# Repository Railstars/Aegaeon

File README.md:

Aegaeon
=======

A feature-rich, NMRA standards compliant DCC decoder built around the Atmel ATtiny84A.

This project comprises hardware, firmware, and documentation for the Railstars Aegaeon series of [NMRA DCC decoders](http://en.wikipedia.org/wiki/Digital_Command_Control).

The Intent
----------

Let's be honest: Most decoders manufactured in North America kinda suck. We can do better. I want to harness the power of open source development to put together the finest range of decoders available, anywhere. This project has multiple goals:
* NMRA standard conformance
* Robustness: decoders should be fault-tolerant, and compatible with widest range of other DCC equipment
* Size: Modern technology permits really tiny decoders
* Features: There is no excuse not to have the best feature set possible

Hardware
--------

The hardware features an Atmel ATtiny84A microcontroller, a high-current H-Bridge with BEMF feedback, and two high-current open-collector outputs for lighting effects.

### Features

* Ultra-compact size (approx. 11mm x 6.7mm)
* 1A motor outputs
* Feedback motor control (aka BEMF)
* 16KHz or 32KHz motor operating modes
* Two high-current (300mA) function outputs
* Debugging header for use with DEBUGwire devices like Atmel JTAGICE mk2
* Trimming of internal RC oscillator is necessary for operation, requires Atmel AVRISP, a copy of stk500.exe, and MS DOS to calibrate. (Welcome to the 21st century!)

Firmware
--------

The firmware is written in pure C, and can be conditionally compiled for one of three possible configurations (motor only; motor + two functions; H-Bridge-driven function-only). Feature packed, and fully NMRA standards compliant, guaranteed by a stringent set of unit tests (in UnitTests folder, includes Xcode and NetBeans projects so you can run them straight on your Mac or PC).

### Features

* Momentum, 3-step and 28-step speed tables
* Button-controllable shunting mode
* Configurable function directionality, brightness, and Rule 17 dimming effects
* Configurable, button-controllable animations:
    * Strobe
    * Double strobe
    * Rotary beacon
    * Random flicker
    * Left/right ditch lights
    * Mars and Gyra lights
* Optional soft-start lighting effect
* Advanced consisting
* Supports Paged, Direct, Physical, and Operations mode programming
* Configurable DC operation, or stop-on-DC.

License
-------

The contents of the firmware folder is licensed under the GPLv3.
All other content is licensed under a Creative Commons Attribution-ShareAlike 3.0 Unported license

The Future
----------

There are a large number of features I would like to add to this product. I need your help!
- [ ] 2-layer PCB with easy-to-solder components for DIY
- [ ] ATmega328p/AT90CAN128 support for Arduino Uno/Railstars Io:duino
- [ ] Visual Studio project for unit tests
- [ ] Arduino project for easy integration into Arduino projects
- [ ] RailCom support (Railstars has a license to the necessary patents to implement RailCom, need to verify that implementing it as an open source project is kosher)
- [ ] On-the-tracks ops-mode bootloader. Ideally Arduino compatible but that might be a stretch. Would certainly require RailCom to work. But wouldn't that be awesome!?

Discussion
----------

You can get support for the Aegaeon software at the Railstars [Support Forum](http://support.railstars.com/index.php?p=/categories/aegaeon-firmware)

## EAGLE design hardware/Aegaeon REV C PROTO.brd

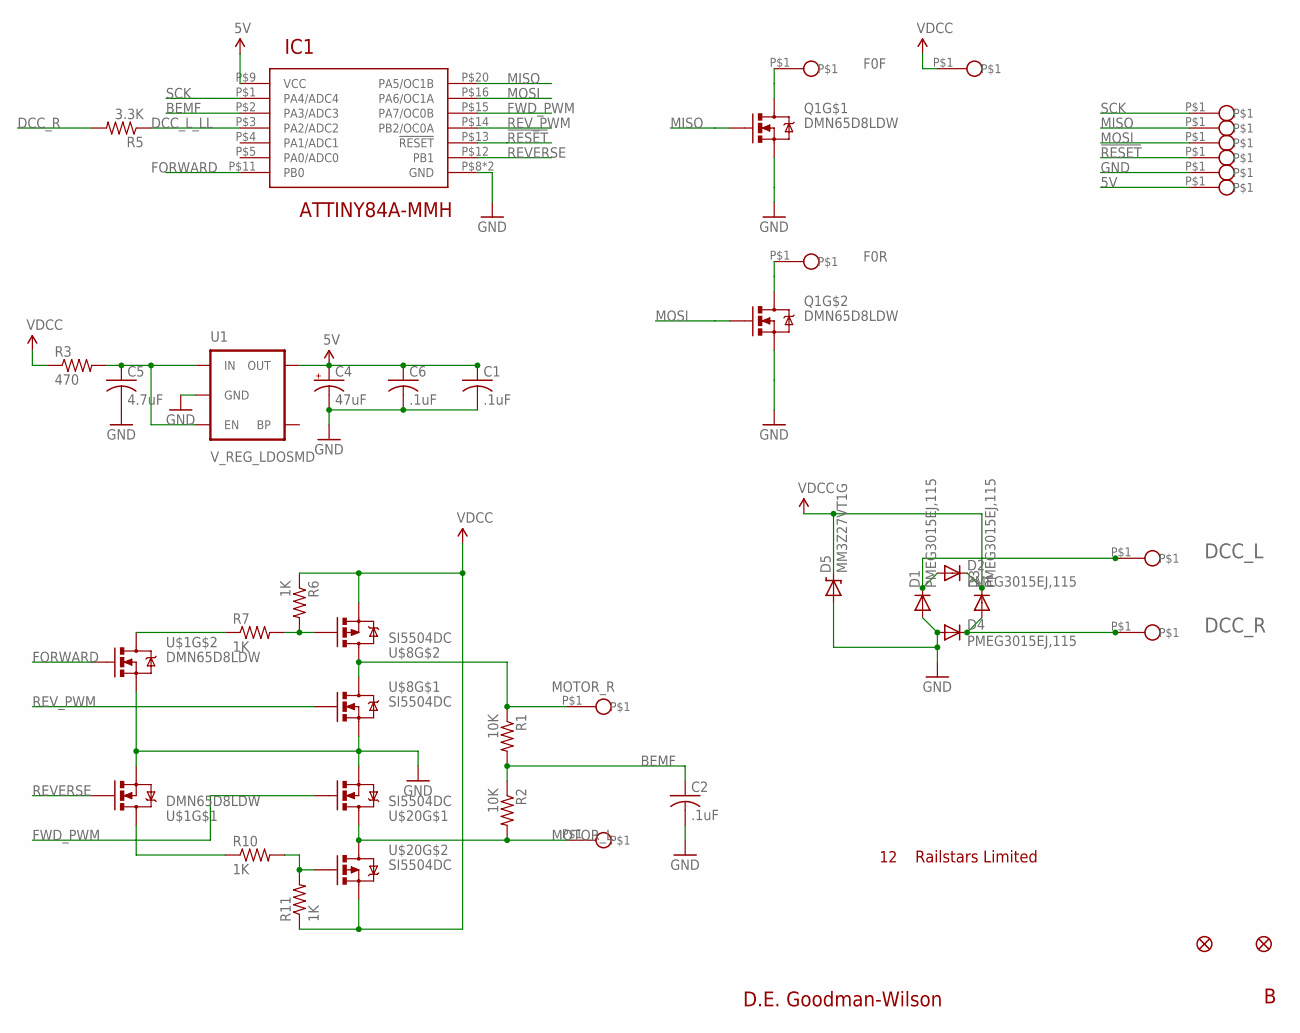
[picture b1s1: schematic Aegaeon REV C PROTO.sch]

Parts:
C1: .1uF; C0201
C2, C6: .1uF; C0402
C4: 47uF; CPOL0603
C5: 4.7uF; C0603
D1, D2, D3, D4: PMEG3015EJ,115; SOD-323
D5: MM3Z27VT1G; SOD-323
DCC_L: PAD1MM; LED_SOLDER_PAD
DCC_R: PAD1MM; LED_SOLDER_PAD
IC1: ATTINY84A-MMH; VQFN-20
JP2, JP4: FIDUCIALUFIDUCIAL; MICRO-FIDUCIAL
Q1: DMN65D8LDW; SOT363
R1, R2: 10K; R0201
R3: 470; R0201
R5: 3.3K; R0201
R6, R7, R10, R11: 1K; R0201
U1: V_REG_LDOSMD; SOT23-5
U$1: DMN65D8LDW; SOT363
U$2, U$3, U$5, U$10, U$11: PAD1MM; LED_SOLDER_PAD
U$8, U$20: SI5504DC; 1206-8
U$14, U$15, U$16, U$17, U$18, U$19: PAD.75MM; POGO_PAD

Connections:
5V: C1.1, C4.1 (+), C6.1, IC1.P$9 (VCC), U1.5 (OUT), U$19.P$1
!RESET: IC1.P$13 (!RESET), U$17.P$1
BEMF: C2.1, IC1.P$2 (PA3/ADC3), R1.2, R2.1
DCC_L: D1.1 (C), D2.2 (A), DCC_L.P$1
DCC_L_LL: IC1.P$3 (PA2/ADC2), R5.1
DCC_R: D3.2 (A), D4.1 (C), DCC_R.P$1, R5.2
F0F: Q1.P$4 (D), U$10.P$1
F0R: Q1.P$1 (D), U$5.P$1
FORWARD: IC1.P$11 (PB0), U$1.P$5 (G)
FWD_PWM: IC1.P$15 (PA7/OC0B), U$20.P$2 (G)
GND: C1.2, C2.2, C4.2 (-), C5.2, C6.2, D1.2 (A), D4.2 (A), D5.2 (A), IC1.P$8 (GND), IC1.P$21 (GND), Q1.P$3 (S), Q1.P$6 (S), U1.2 (GND), U$1.P$3 (S), U$1.P$6 (S), U$8.P$1 (S), U$18.P$1, U$20.P$1 (S)
MISO: IC1.P$20 (PA5/OC1B), Q1.P$2 (G), U$15.P$1
MOSI: IC1.P$16 (PA6/OC1A), Q1.P$5 (G), U$16.P$1
MOTOR_L: R2.2, U$3.P$1, U$20.P$5 (D), U$20.P$6 (D), U$20.P$7 (D), U$20.P$8 (D)
MOTOR_R: R1.1, U$2.P$1, U$8.P$5 (D), U$8.P$6 (D), U$8.P$7 (D), U$8.P$8 (D)
unnamed: R6.2, R7.2, U$8.P$4 (G)
unnamed: C5.1, R3.2, U1.1 (IN), U1.3 (EN)
unnamed: R10.2, R11.2, U$20.P$4 (G)
unnamed: R10.1, U$1.P$4 (D)
unnamed: R7.1, U$1.P$1 (D)
REVERSE: IC1.P$12 (PB1), U$1.P$2 (G)
REV_PWM: IC1.P$14 (PB2/OC0A), U$8.P$2 (G)
SCK: IC1.P$1 (PA4/ADC4), U$14.P$1
VDCC: D2.1 (C), D3.1 (C), D5.1 (C), R3.1, R6.1, R11.1, U$8.P$3 (S), U$11.P$1, U$20.P$3 (S)

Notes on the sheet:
Railstars Limited
D.E. Goodman-Wilson

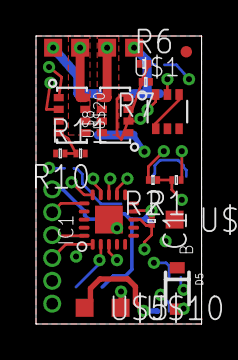
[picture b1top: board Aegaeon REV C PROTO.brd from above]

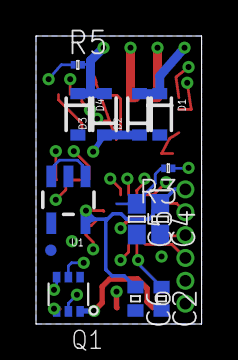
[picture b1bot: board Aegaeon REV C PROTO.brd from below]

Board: 4 copper layers, 9.2 x 16.0 mm, 39 parts (13 on the bottom side), 24 nets.

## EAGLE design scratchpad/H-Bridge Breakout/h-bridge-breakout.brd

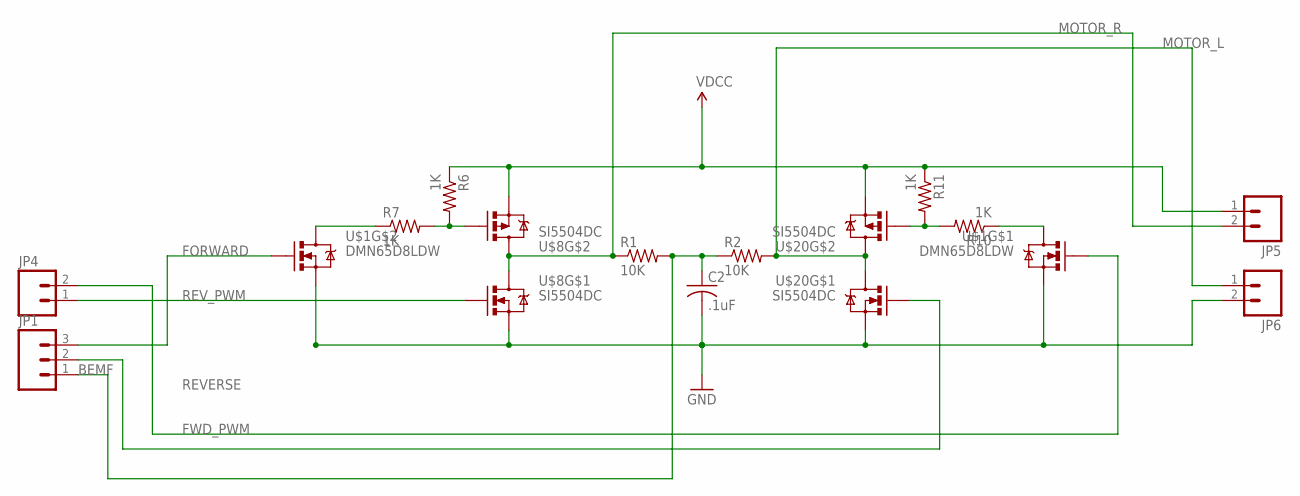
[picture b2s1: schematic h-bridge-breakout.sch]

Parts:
C2: .1uF; C0402
JP1: M03SCREW; SCREWTERMINAL-3.5MM-3
JP4, JP5, JP6: M023.5MM; SCREWTERMINAL-3.5MM-2
R1, R2: 10K; R0603
R6, R7, R10, R11: 1K; R0603
U$1: DMN65D8LDW; SOT363
U$8, U$20: SI5504DC; 1206-8

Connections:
BEMF: C2.1, JP1.1, R1.2, R2.1
FORWARD: JP1.3, U$1.P$5 (G)
FWD_PWM: JP1.2, U$20.P$2 (G)
GND: C2.2, JP6.2, U$1.P$3 (S), U$1.P$6 (S), U$8.P$1 (S), U$20.P$1 (S)
MOTOR_L: JP6.1, R2.2, U$20.P$5 (D), U$20.P$6 (D), U$20.P$7 (D), U$20.P$8 (D)
MOTOR_R: JP5.2, R1.1, U$8.P$5 (D), U$8.P$6 (D), U$8.P$7 (D), U$8.P$8 (D)
unnamed: R6.2, R7.2, U$8.P$4 (G)
unnamed: R10.2, R11.2, U$20.P$4 (G)
unnamed: R10.1, U$1.P$4 (D)
unnamed: R7.1, U$1.P$1 (D)
REVERSE: JP4.2, U$1.P$2 (G)
REV_PWM: JP4.1, U$8.P$2 (G)
VDCC: JP5.1, R6.1, R11.1, U$8.P$3 (S), U$20.P$3 (S)

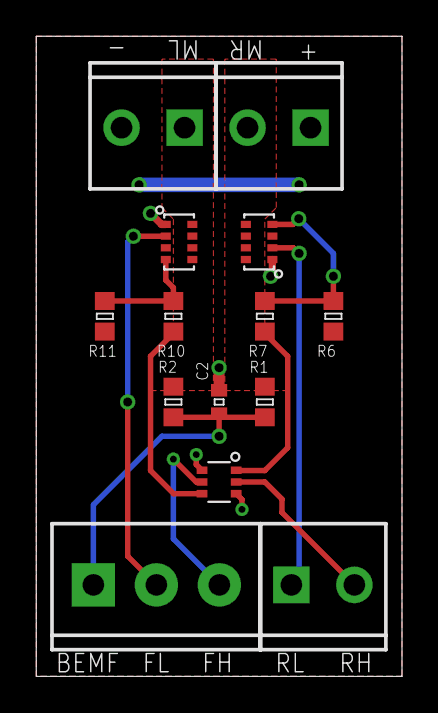
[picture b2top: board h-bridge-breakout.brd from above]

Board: 2 copper layers, 20.3 x 35.6 mm, 14 parts (0 on the bottom side), 13 nets.

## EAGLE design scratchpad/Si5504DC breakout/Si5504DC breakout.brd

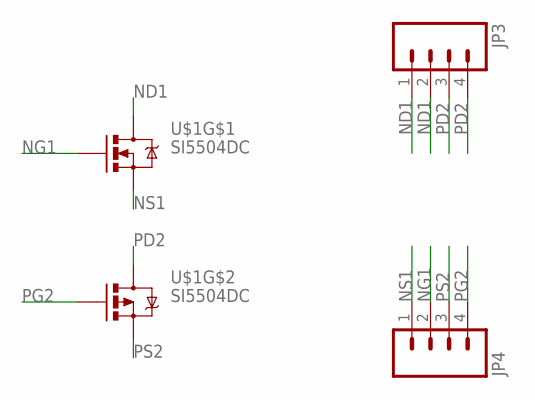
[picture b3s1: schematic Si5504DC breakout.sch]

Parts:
JP3, JP4: M04LOCK; 1X04_LOCK
U$1: SI5504DC; 1206-8

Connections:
ND1: JP3.1, JP3.2, U$1.P$7 (D), U$1.P$8 (D)
NG1: JP4.2, U$1.P$2 (G)
NS1: JP4.1, U$1.P$1 (S)
PD2: JP3.3, JP3.4, U$1.P$5 (D), U$1.P$6 (D)
PG2: JP4.4, U$1.P$4 (G)
PS2: JP4.3, U$1.P$3 (S)

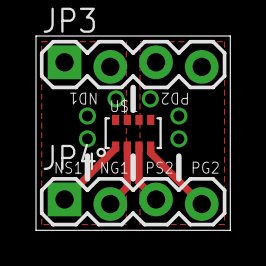
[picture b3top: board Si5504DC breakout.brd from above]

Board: 2 copper layers, 10.8 x 10.8 mm, 3 parts (0 on the bottom side), 6 nets.

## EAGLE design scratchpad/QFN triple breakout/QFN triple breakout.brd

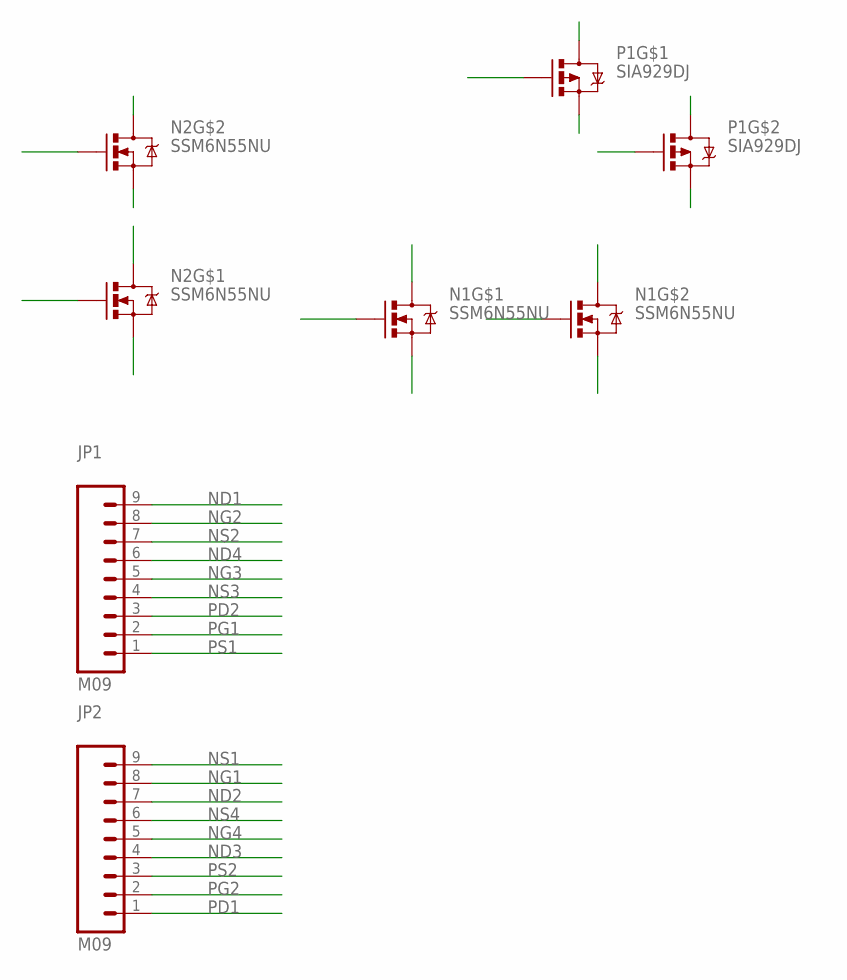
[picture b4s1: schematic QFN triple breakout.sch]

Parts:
JP1, JP2: M09; 1X09
N1, N2: SSM6N55NU; UDFN6
P1: SIA929DJ; SC70-6L

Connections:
ND1: JP1.9, N2.D2 (D), N2.D2$2 (D)
ND2: JP2.7, N2.D1 (D), N2.D1$1 (D)
ND3: JP2.4, N1.D1 (D), N1.D1$1 (D)
ND4: JP1.6, N1.D2 (D), N1.D2$2 (D)
NG1: JP2.8, N2.G2 (G)
NG2: JP1.8, N2.G1 (G)
NG3: JP1.5, N1.G1 (G)
NG4: JP2.5, N1.G2 (G)
NS1: JP2.9, N2.S2 (S)
NS2: JP1.7, N2.S1 (S)
NS3: JP1.4, N1.S1 (S)
NS4: JP2.6, N1.S2 (S)
PD1: JP2.1, P1.D1 (D), P1.D1$2 (D)
PD2: JP1.3, P1.D2 (D), P1.D2$2 (D)
PG1: JP1.2, P1.G1 (G)
PG2: JP2.2, P1.G2 (G)
PS1: JP1.1, P1.S1 (S)
PS2: JP2.3, P1.S2 (S)

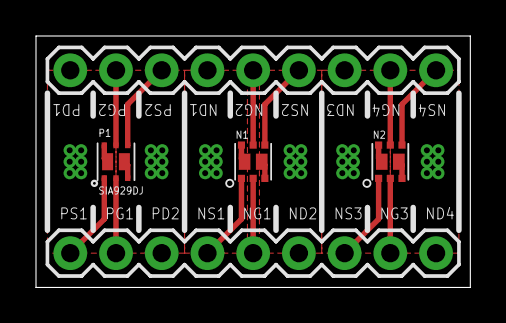
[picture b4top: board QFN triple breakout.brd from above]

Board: 2 copper layers, 24.1 x 14.0 mm, 5 parts (0 on the bottom side), 18 nets.

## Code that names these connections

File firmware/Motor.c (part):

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#include "Motor.h"
#include "globals.h"

#define ENABLE (1<<PB1)
#define FX_SHUNTING (1<<6)

volatile uint8_t sample, sample_ready, min_ADC;
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    else return retval;
}

//                  PB0 (fwd)   PB1 (rev)   PA7 (fpwm)  PB2 (rpwm)
//FORWARD =         HIGH        LOW         HIGH        LOW
//REVERSE =         LOW         HIGH        LOW         HIGH
//BRAKE   =         HIGH        HIGH        LOW         LOW
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    //do other things to set up the hardware.
    //on ATtiny84A, setup TIMER0 for both motor control PWM on output compare B and a millis timer on compare match overflow
    
    //set PB0, PB1, PA7, and PB2 to output, and bring all low
    DDRB |= (1 << DDB0) | (1 << DDB1) | (1 << DDB2);
    DDRA |= (1 << DDA7);
    PORTB &= ~(1 << PB0) & ~(1 << PB1) & ~(1 << PB2); //set all these LOW
    PORTA &= ~(1 << PA7);
    
    
    TCCR0A = (1 << WGM00); // phase correct PWM
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#endif //USE_BEMF
    
    _eStop = 0;
    _current_speed = _goal_speed = 1; //forward stop
    min_ADC = 0x93;
}

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        Output_Match[0] = Output_Match_Buf[0];
        Output_Match[1] = Output_Match_Buf[1];
        if (Output_Match[0])
            PORTA |= (1 << PA5); //only turn on if match is non-zero! Prevents flicker when should be off.
        if (Output_Match[1])
            PORTA |= (1 << PA6);
    }
    
    if (Output_Match[0] == softcount) //just rolled over, turn output off
    {
        PORTA &= ~(1 << PA5);
    }
    if (Output_Match[1] == softcount) //just rolled over, turn output off
    {
        PORTA &= ~(1 << PA6);
    }
#endif //USE_FX
    
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#ifdef USE_MOTOR
    //NMRA requires that we remove power from motor. We do this by setting out motor lines LOW.
    TCCR0A &= ~(1 << COM0A0) & ~(1 << COM0A1) & ~(COM0B0) & ~(COM0B1); //disconnect PWM from timer
    PORTB &= ~(1 << PB0) & ~(1 << PB1) & ~(1 << PB2); //force all four motor control lines LOW, turns off motor.
    PORTA &= ~(1 << PA7); //these two lines may not be necessary. Possibly even dangerous.

#endif //USE_MOTOR
    
    _eStop = 1;
    if (dir >= 0)
        _current_speed = _goal_speed = 1; //immediate forward stop
    else
        _current_speed = _goal_speed = -1; //immediate reverse stop
    //_voltage_level = _voltage_adjust = 0; //make sure we don't re-energize!
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        //first, set the h-bridge to coast
        //set OC0A first to avoid a shoot-through condition
        TCCR0A &= ~(1 << COM0A0) & ~(1 << COM0A1) & ~(COM0B0) & ~(COM0B1); //disconnect PWM from timer
        PORTB &= ~(1 << PB0) & ~(1 << PB1) & ~(1 << PB2); //force all four motor control lines LOW, turns off motor.
        PORTA &= ~(1 << PA7); //these two lines may not be necessary. Possibly even dangerous.
        //start an AD conversion
        ADCSRA |= (1 << ADSC);
    }
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                if (_current_speed < 0) //if negative
                {
                    //set REVERSE ENABLE
                    PORTB &= ~(1 << PB0); //must bring this pin low first, to avoid shoot-through
                    _delay_loop_1(1); //pause for three cycles;
                    PORTB |=  (1 << PB1); //reverse enable
#ifdef USE_MOTOR_FOR_FX
                    voltage = Output_Match_Buf[1];
#else //use motor for motor
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                {
                    //set FORWARD ENABLE
                    //set REVERSE ENABLE
                    PORTB &= ~(1 << PB1); //must bring this pin low first, to avoid shoot-through TODO IS THIS TRUE NOW I don't think so. I think we have a different condition to worry about
                    _delay_loop_1(1); //pause for three cycles;
                    PORTB |=  (1 << PB0); //forward enable
#ifdef USE_MOTOR_FOR_FX
                    voltage = Output_Match_Buf[0];
#else //use motor for motor
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
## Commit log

2013-07-14 First commit of code. This code has been a long time in the making...
2013-07-14 added ignore for build dirs
2013-07-14 Improved the debug build by automatically cutting off features that interfere with debugging.
2013-07-14 Restructured the repo ever so slightly
2013-07-14 Adding files for automating clock calibration and firmware installation. This all needs to be organized pretty badly
2013-07-14 Added schematics and PCB layouts for latest version of prototypes and production types.
2013-07-14 Minor configuration changes to repo
2013-07-14 Slight update to .gitignore.
2013-07-14 Added documentation to repo
2013-07-14 Began adding firmware installation. Not yet working. Requires stk500.exe
2013-07-14 Structural changes so compiled images are ignored.
2013-07-14 Clock calibration and install script working!
2013-07-14 First phase of bringing the three projects together complete.
2013-07-14 Progress on merging the three projects!
2013-07-15 L2 and M merged.
2013-07-15 Removed :M specific project
2013-07-15 Cleanup
2013-07-15 Tentative merging of :C into single codebase. Requires testing.
2013-07-15 Updates to the user manual.
2013-07-15 Corrections and editing to the user manual.
2013-07-15 Documented TODOs in manual
2013-08-08 Added a breakout for the MOSFETs to the scratchpad
2013-08-08 Fixed typo on silkscreen
2013-08-08 Updated with OSHPark design rules
2013-08-08 Added some helpful silkscreen
2013-08-08 Changed a couple of part numbers to make more sense.
2013-08-08 Adjusted thermal spacing
2013-09-23 Added a line to choose which decoder to compile for.
2013-09-23 Unnecessary defines in DCC_Config.h removed.
2013-09-23 Added licensing information
2013-09-23 Typos in README
2013-09-24 Fixed typo bug in DCC_Packet_Zero
2013-09-24 Indentation and presentations changes.
2013-09-24 Fixed bug where FX outputs are never updated on 'C
2013-09-24 refactored decoder-specific conditional compiles
2013-10-05 A scratchpad branch to start integrating the unit tests I'd made.
2013-10-05 More refined .gitignore
2013-10-05 Even more refinements to .gitignore
2013-10-05 Progress. Defining decoder-based build settings. Updated to NetBeans 7.3.1.
2013-10-05 Removed old decoder files, replaced with references to actual code.
2013-10-05 Combined testing and production reset files.
2013-10-05 More files to ignore!
2013-10-05 Makefiles seem to be in order. Tests need to be updated to latest signatures—wow are they out of date!
2013-10-05 Unittests compile, but fail. No real surprise there as some of the interfaces have changed.
2013-10-05 Updated some of the motor output settings in tests. Moved to CLang, since GNU isn't supported on my dev platform anymore (OS X Mavericks)
2013-10-06 Cleaned up many of the motor tests, although more work to do. Refined settings for GCC to match my installs on Mavericks, which are a bit non-standard. Debugger still not quite working, although YMMV.
2013-10-07 Added Xcode project, because I was tired of banging my head against a wall getting NetBeans to work again. Left NetBeans project intact in case someone else wants to use it—it should be fine on most 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
2013-10-07 Unit tests now run, though they fail for a variety of reasons. Still lots of repair work to do to make them work with the current hardware configuration.
2013-10-07 Fixed minor logic bug in motor control.
2013-10-07 Repaired some of the basic decoder tests.
2013-10-07 Removed a few unnecessary comments.
2013-10-07 Deleted from repo user-settings in Xcode project.
2013-10-07 Added some helpful comments.
2013-10-07 Fixes #1 and any other tests that depend on behavior of full speed, or stopped speeds.
2013-10-07 Added hardware-independent macros for FX status
2013-10-07 Fixed an off-by-one error in (FXTests, BasicFXCommandOn_50percentdim)
2013-10-07 Closes #2
2013-10-07 Neatened up tests (FXTests, BasicFXCommandOn_50percentdim) and (FXTests, BasicFXCommandOn_Rule17_Stop_Dim_V1). Others likely could use the same treatment.
2013-10-07 More of the same kinds of minor fixes.
2013-10-07 Closes #3. Also prettifies some of the FX_Test Rule17 tests.
2013-10-07 Closes #4
2013-10-07 Added hardware defs and test for motor deenergized at start.
2013-10-07 Added hardware defs to testing motor direction, and have begun updating motor tests to proeprly test for this now. Previously, direction was tied up with the PWM output. New method of testing is indp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
2013-10-07 Closes #6 Closes #7
2013-10-08 Updated Xcode project to compile on OS X 10.7 or later
2013-10-08 Closes #8.
2013-10-09 Fixed a problem with (MotorTests, TestAccelDecel_v1)
2013-10-09 Added better comments to estop(). Fixed estop test to reflect actual conditions during an estop.
2013-10-09 Fixed the motor initialization test to reflect that initial conditions should be braked, not deenergized
2013-10-09 Fixed a typo in (MotorTests, Initialization)
2013-10-09 Closes #10
2013-10-10 Closes #9
2013-10-10 Whitespaces changes to motor.c only.
2013-10-10 Closes #11
2013-10-10 Closes #12
2013-10-10 Closes #16
2013-10-11 Closes #15. The problem was a typo in the test!
2013-10-11 Clarified some of the code in (NMRAMotorDecoderTests, PagedModeAddressWrite) for #15.
2013-10-11 Fixed a silently failing typo in (NMRAMotorDecoderTests, PagedModeAddressWrite) and added (NMRAMotorDecoderTests, PagedModeArbitraryCVWrite), to be refined.
2013-10-11 Made (NMRAMotorDecoderTests, PagedModeArbitraryCVWrite) more sophisticated—can be changed for any CV easily.
2013-10-11 Fixed error in (NMRAMotorDecoderTests, PagedModeAddressWrite)
2013-10-11 Closes #14. The problem, in fact, was a combination of bad code and bad tests. Basically, the direction flag in CV19 was being set wrong and tested wrong! But the reinforcing tests did eventually cat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
2013-10-11 Closes #13. The problem was a minor typo in (NMRAMotorDecoderTests, AddressPartitionTest). Refactored the test slightly to increase readability. The test, as it happens, is ludicrous, but necessary, 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
2013-10-12 Updated README to reflect new status of unit tests.
2013-10-12 Added intent section to README
2013-10-12 Adding circuit.jar simulation of H-Bridge pursuant to solving #17.
2013-10-12 Fixed typos in README
2013-10-13 Add a Bitdeli badge to README
2013-10-15 Updated simulation of H-Bridge with new schematic from Karl Kobel.
2013-10-16 Updated proto schematics to match new bridge design. Streamlined design in simulation file.
2013-10-16 Minor tweaking of schematic layout.
2013-10-16 Saved files.
2013-10-16 Changed motor to initialize to all pins LOW. In new bridge, this disables all switches.
2013-10-16 Updated motor speed tests to reflect new bridge design.
2013-10-16 Fixed hardware definition for measuing PWM levels.
2013-10-16 Decoder firmware now passes all tests again.
2013-10-16 Reverted to 6.1.0 format.
2013-10-16 Filling in the blanks in the documentation
2013-10-16 Edits to FAQ
2013-10-24 Added intrinsic diodes to MOSFETs in simulation.
2013-10-25 Added dead time delay to motor outputs when switching direction.
2013-10-25 Updated the tests to include ignored tests that should not be ignored
2013-10-25 Reworked accessory packet detection tests, which are passed.
2013-11-22 Fixed error on QFN triple breakout silk.
2013-11-25 Changes to AVRStudio project to get it to compile and download. Not entirely sure what the changes comprise in.
2013-11-25 Added a breakout board for the SI5504DC MOSFET half-bridge.
2013-11-25 Initial commit for H-Bridge designed with SI5504DC parts.
2014-02-18 Moved vias, and added solder resist to tent vias.
2014-02-18 Added CAM files to .gitignore
2014-03-02 Working on the layout a bit? Lost track of where I was.
2014-03-04 Redesigning the H-Bridge. This one seems to work under test.
2014-03-04 Set up new defines for desired motor output states.
2014-03-04 Removed typos in unittest defines
2014-03-04 Improved motor initialization test—begins coasting, not braked
2014-03-04 Motor initialization passes
2014-03-04 Added motor shootthru tests
2014-03-04 Added one more shoothru test
2014-03-04 Timers should be hooked up correctly now. Timer outputs need to be wired.
2014-03-05 Lots of logic fixes to motor control code. Not entirely confident that they are right. At all.
2014-03-05 Fixed some motor checking constants
2014-03-05 More motor constant fixes
2014-03-05 Improved motor tests. All logic tests pass. Crazy. This can't be right.
2014-04-14 Added a h-bridge breakout board to the scratchpad.
    Just built one of these, and the darned thing doesn't seem to work. A bit mystified as to why that might be.
2014-07-12 Added simulation for use with circuit.jar
2014-10-20 Unsure why this got renamed, but there it is.
2014-10-20 Feels like we're headed down a rabbit hole.

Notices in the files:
hardware/Aegaeon REV C PROTO.brd:
Copyright (C) 2012, Railstars Limited
All Rights Reserved
parts and their libraries:
SparkFun-Aesthetics: Licensing: CC v3.0 Share-Alike You are welcome to use this library for commercial purposes.
Railstars: Copyright C 20
